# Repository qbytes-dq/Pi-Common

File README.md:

# Pi-Common
RaspberryPi Common Components

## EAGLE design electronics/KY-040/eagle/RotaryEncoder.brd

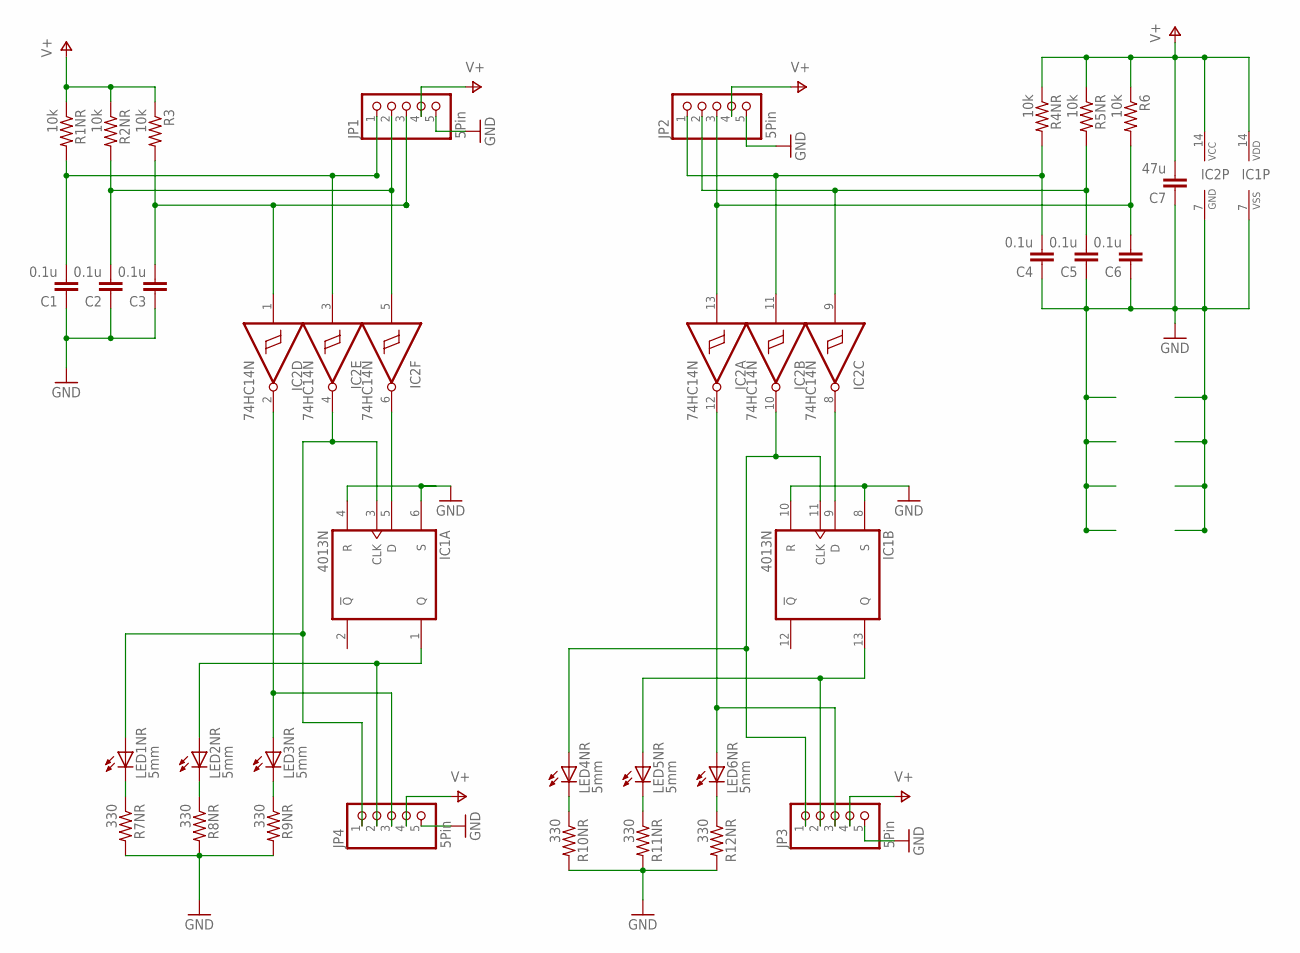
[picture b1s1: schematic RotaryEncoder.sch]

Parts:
C1, C2, C3, C4, C5, C6: 0.1u; C7.5B3
C7: 47u; C7.5B3
IC1: 4013N; DIL14
IC2: 74HC14N; DIL14
JP1, JP2, JP3, JP4: 5Pin; 1X05
LED1NR, LED2NR, LED3NR, LED4NR, LED5NR, LED6NR: 5mm; LED5MM
R1NR, R2NR, R3, R4NR, R5NR, R6: 10k; 0411/15
R7NR, R8NR, R9NR, R10NR, R11NR, R12NR: 330; 0411/15

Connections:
GND: C1.1, C2.1, C3.1, C4.1, C5.1, C6.1, C7.1, IC1.4 (R), IC1.6 (S), IC1.7 (VSS), IC1.8 (S), IC1.10 (R), IC2.7 (GND), JP1.5, JP2.5, JP3.5, JP4.5, R7NR.2, R8NR.2, R9NR.2, R10NR.2, R11NR.2, R12NR.2
unnamed: C4.2, IC2.11 (I), JP2.1, R4NR.2
unnamed: C1.2, IC2.3 (I), JP1.1, R1NR.2
unnamed: C2.2, IC2.5 (I), JP1.2, R2NR.2
unnamed: C3.2, IC2.1 (I), JP1.3, R3.2
unnamed: LED1NR.K (C), R7NR.1
unnamed: IC2.12 (O), JP3.3, LED6NR.A
unnamed: C6.2, IC2.13 (I), JP2.3, R6.2
unnamed: C5.2, IC2.9 (I), JP2.2, R5NR.2
unnamed: IC1.5 (D), IC2.6 (O)
unnamed: IC2.2 (O), JP4.3, LED3NR.A
unnamed: IC1.1 (Q), JP4.2, LED2NR.A
unnamed: IC1.3 (CLK), IC2.4 (O), JP4.1, LED1NR.A
unnamed: LED2NR.K (C), R8NR.1
unnamed: LED3NR.K (C), R9NR.1
unnamed: LED4NR.K (C), R10NR.1
unnamed: IC1.13 (Q), JP3.2, LED5NR.A
unnamed: IC1.11 (CLK), IC2.10 (O), JP3.1, LED4NR.A
unnamed: IC1.9 (D), IC2.8 (O)
unnamed: LED6NR.K (C), R12NR.1
unnamed: LED5NR.K (C), R11NR.1
V+: C7.2, IC1.14 (VDD), IC2.14 (VCC), JP1.4, JP2.4, JP3.4, JP4.4, R1NR.1, R2NR.1, R3.1, R4NR.1, R5NR.1, R6.1

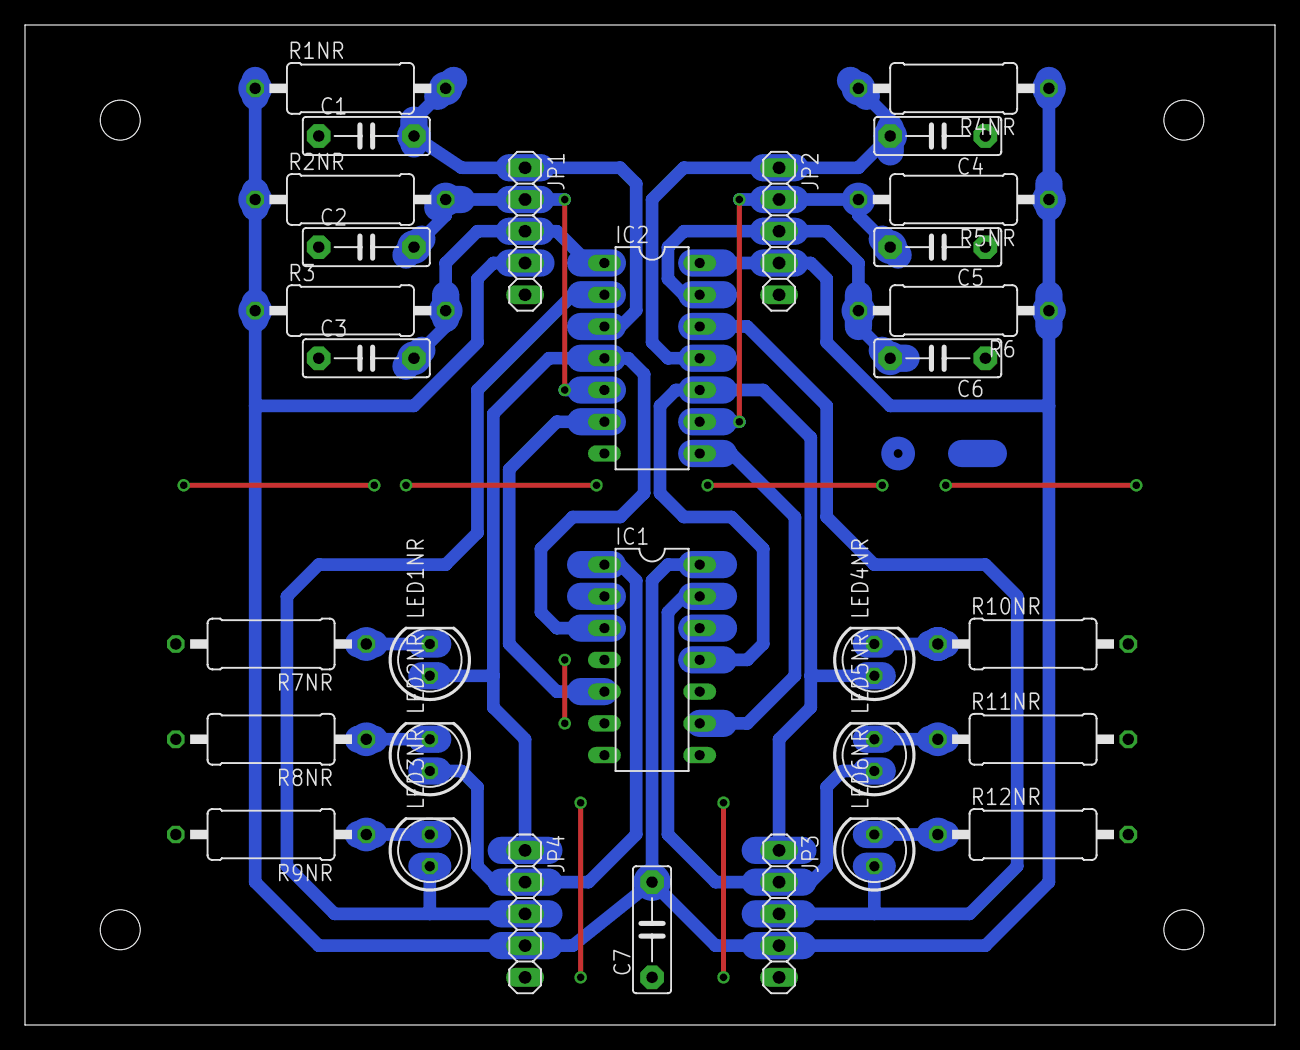
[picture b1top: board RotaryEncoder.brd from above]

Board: 2 copper layers, 100.0 x 80.0 mm, 31 parts (0 on the bottom side), 22 nets.

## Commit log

2016-09-19 Adding Rotary Encoder
2016-09-20 Added AutoLevel and AutoLevel with PCB mill.
2016-09-22 Update fm Tuner
